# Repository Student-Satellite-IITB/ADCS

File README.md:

# ADCS
Attitude Determination and Control Subsystem of the CubeSat

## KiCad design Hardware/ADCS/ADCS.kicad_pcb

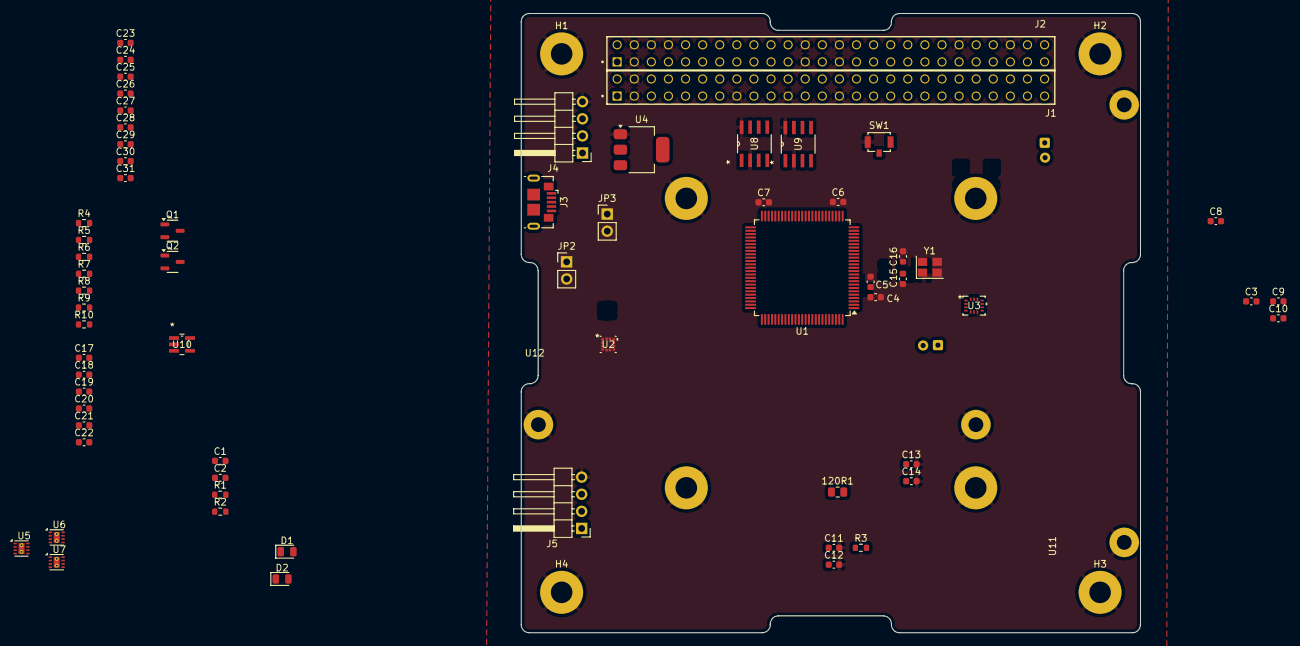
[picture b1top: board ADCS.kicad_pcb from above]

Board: 4 copper layers, 92.0 x 92.0 mm, 72 parts (1 on the bottom side), 41 nets, no tracks yet.

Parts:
120R1: FerriteBead; R_0805_2012Metric
C1, C2: 22uF; C_0603_1608Metric
C3, C21, C25, C27, C30: 10uF; C_0603_1608Metric
C4, C5, C6, C7, C8, C9, C10, C14, C17, C18, C19, C20: 100nF; C_0603_1608Metric
C11: 10nF; C_0603_1608Metric
C12, C13: 1uF; C_0603_1608Metric
C15, C16: 10pF; C_0603_1608Metric
C22: 220nF; C_0603_1608Metric
C23, C24, C26, C28, C29, C31: 0.1uF; C_0603_1608Metric
D1: ADCS_5V_LED; LED_0805_2012Metric
D2: ADCS_3V3_LED; LED_0805_2012Metric
H1, H2, H3, H4: MountingHole_Pad; MountingHole_3.2mm_M3_Pad
J1, J2: Conn_02x26_Odd_Even; SAMTEC_ESQ-126-39-G-D
J3: USB_B_Micro; USB_Micro-B_GCT_USB3076-30-A
J4, J5: Conn_01x04_Pin; PinHeader_1x04_P2.54mm_Horizontal
JP2, JP3: USB_POW_EN; PinHeader_1x02_P2.54mm_Vertical
Q1, Q2: PMOS; SOT-23-3
R1, R2, R4, R5: 1k5; R_0603_1608Metric
R3: 10k; R_0603_1608Metric
R6, R8: 100k; R_0603_1608Metric
R7, R9: 100; R_0603_1608Metric
R10: 0; R_0603_1608Metric
SW1: SW_SPDT; SW_SPST_B3U-1100P
U1: STM32L471VET6; LQFP-100_14x14mm_P0.5mm
U2: IIS2MDCTR; LGA-12_2X2X0P7_STM
U3: BMI270; BMI270_BOS
U4: AMS1117-3.3; SOT-223-3_TabPin2
U5, U6, U7: DRV8212P; WSON-8-1EP_2x2mm_P0.5mm_EP0.9x1.6mm_ThermalVias
U8, U9: SN65HVD256D; D8
U10: TPS3824-33QDBVRQ1; tps3824
U11, U12: MTQ_ROD
U13: MTQ_AIRCORE
Y1: 32MHz; Crystal_SMD_Abracon_ABM8AIG-4Pin_3.2x2.5mm

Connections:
3V3_ADCS: 120R1.2, C3.1, C4.1, C5.1, C6.1, C7.1, C8.1, C9.1, C10.1, C13.1, C17.1, C18.1, C19.1, C20.1, C21.1, C23.1, C28.1, C31.1, D2.2 (A), J2.39, J2.40, J4.1, J5.1, JP3.2 (B), R4.1, R5.1, SW1.3 (C), U1.6 (VBAT), U1.11 (VDD), U1.22 (VDDA), U1.28 (VDD), U1.50 (VDD), U1.73 (VDD), U1.75 (VDD), U2.3 (CS), U2.9 (VDD), U2.10 (VDD_IO), U3.5 (VDDIO), U3.8 (VDD), U3.12 (CSB), U5.8 (VCC), U6.8 (VCC), U7.8 (VCC), U8.5 (VRXD), U9.5 (VRXD), U10.5 (VDD)
5V_ADCS: C24.1, C25.1, C26.1, C27.1, C29.1, C30.1, D1.2 (A), J2.37, J2.38, JP2.2 (B), Q1.3 (S), Q2.3 (S), R6.2, R8.2, U5.1 (VM), U6.1 (VM), U7.1 (VM)
+3.3VA: 120R1.1, C11.1, C12.1, U1.100 (VDD)
/3V3_ANT: J2.5, J2.7
/3V3_EPS: J1.31, J1.32
/3V3_LDO: C2.1, JP3.1 (A), U4.2 (VO)
/5V_COMM: J1.47, J1.49
/5V_EPS: J1.29, J1.30
/5V_OBC: J2.29, J2.30
/5V_PAY: J2.25, J2.26
/12V_ADCS: J2.31, J2.32
/CAN_A_H: J1.19, U8.7 (CANH)
/CAN_A_L: J1.17, U8.6 (CANL)
/CAN_B_H: J1.25, U9.7 (CANH)
/CAN_B_L: J1.23, U9.6 (CANL)
/ControlUnit/BOOT0: R3.2, U1.94 (BOOT0)
/ControlUnit/CAN_RX: U8.4 (RXD), U9.4 (RXD)
/ControlUnit/CAN_TX: U8.1 (TXD), U9.1 (TXD)
/ControlUnit/HSE_IN: C15.1, U1.12 (PH0), Y1.1
/ControlUnit/HSE_OUT: C16.1, U1.13 (PH1), Y1.3
/ControlUnit/NRST: C14.1, R10.2, U1.14 (NRST)
/ControlUnit/PMOS1_GATE: Q1.2 (G), R6.1, R7.2
/ControlUnit/PMOS2_GATE: Q2.2 (G), R8.1, R9.2
/ControlUnit/SW_BOOT0: R3.1, SW1.2 (B)
/ControlUnit/WDI_RESET: R10.1, U10.3 (RESET)
/I2C_SCL: R5.2, U2.1 (SCL/SPC), U3.13 (SCX)
/I2C_SDA: R4.2, U2.4 (SDA/SDI/SDO), U3.14 (SDX)
/LED_CATHODE: D2.1 (K), R2.1
/MTQ/MTQY_1: U6.2 (OUT1), U12.1 (IN1)
/MTQ/MTQY_2: U6.3 (OUT2), U12.2 (IN2)
/MTQ/MTQZ_1: U7.2 (OUT1), U11.1 (IN1)
/MTQ/MTQZ_2: U7.3 (OUT2), U11.2 (IN2)
/USB_D+: J3.3 (D+), U1.71 (PA12)
/USB_D-: J3.2 (D-), U1.70 (PA11)
/VBUS0: J1.1, J1.2, J2.1, J2.2
GND: C1.2, C2.2, C3.2, C4.2, C5.2, C6.2, C7.2, C8.2, C9.2, C10.2, C11.2, C12.2, C13.2, C14.2, C15.2, C16.2, C17.2, C18.2, C19.2, C20.2, C21.2, C22.2, C23.2, C24.2, C25.2, C26.2, C27.2, C28.2, C29.2, C30.2, C31.2, H1.1, H2.1, H3.1, H4.1, J1.3, J1.4, J1.15, J1.21, J1.27, J2.3, J2.4, J2.6, J2.8, J2.23, J2.24, J2.27, J2.28, J2.42, J2.48, J3.5 (GND), J4.4, J5.4, R1.2, R2.2, SW1.1 (A), U1.10 (VSS), U1.19 (VSSA), U1.27 (VSS), U1.49 (VSS), U1.74 (VSS), U1.99 (VSS), U2.6 (GND), U2.8 (GND), U3.1 (SDO), U3.6 (GNDIO), U3.7 (GND), U4.1 (GND), U5.4 (GND), U5.9 (GND), U6.4 (GND), U6.9 (GND), U7.4 (GND), U7.9 (GND), U8.2 (GND), U8.8 (S), U9.2 (GND), U9.8 (S), U10.2 (GND), U11.3 (GND), U11.4 (GND), U12.3 (GND), U12.4 (GND), U13.3 (GND), U13.4 (GND), U13.5 (GND), U13.6 (GND), Y1.2, Y1.4
unnamed: D1.1 (K), R1.1
unnamed: Q1.1 (D), U8.3 (VCC)
unnamed: Q2.1 (D), U9.3 (VCC)
unnamed: C22.1, U2.5 (C1)
VUSB: C1.1, J3.1 (VBUS), JP2.1 (A), U4.3 (VI)

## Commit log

2024-06-24 Organised filesystem
2024-06-24 Added Actuator filesystem
2024-06-24 Added cubesat_dynamics_model in Dynamics-and-Modelling
2024-06-24 Updated README.md to include information on the folder added of the model.
2024-06-24 Create .gitignore
    Added MATLAB gitignore to ignore cache files and autosaves, etc.
2024-06-25 Removed unnecessary files and updated documentation
2024-06-25 Updated README.md to contain live documentation slides link
2024-06-25 Add air core MTQ simulation
    Might add a power output if necessary
2024-06-25 Delete MTQ_Simulation.slx to re-add it in a dedicated folder
    It's good practice
2024-06-25 Create MTQ_Simulation directory and add the models there
    Better organization
2024-06-28 Create Torque_Rod_Sim
    Resistance calculation was tricky. Power calculation can be done if hysteresis graph is known (smaller the graph width, lesser inductive losses)
2024-07-01 Fixed the self made Dynamic Block, modelled reaction wheel and updated 'ReadMe.pdf
2024-09-05 Added CubeSat Simulation Model and Gyro Model
2024-10-26 ADCS Hardware Design started
    Started ADCS Board Schematic
2024-10-28 ADCS PCB Schematic
    Progress in Schematic
    Added STM32 Project
2024-10-30 ADCS PCB Rough Layout
2024-12-06 Fixed a bug in ECI2LVLH function and changed inertial frame to ECI from LVLH
2024-12-17 Updated dir structure
2024-12-17 renamed dir
2025-07-26 ADCS Design and Analysis scripts - Functional, Logical, Physical Architecture on System Composer - Sequence Diagrams - Software Architecture Diagram - Detumbling - MTQ Sizing
2025-08-07 Maneuver Design, IMU Sizing, MTQ Rod Sizing Updated - MTQ (updated) - RWS and Maneuver Design - IMU - Datasheet for MMC5983MA Magnetometer
